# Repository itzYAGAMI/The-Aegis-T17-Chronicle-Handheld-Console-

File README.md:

# THE AEGIS-T17 CHRONICLE

*This is a pocket sized Steampunk inspired handheld gaming console featuring four games*

This is the repository for **The Aegis-T17 Chronicle**, a fully playable handheld console powered by the XIAO ESP32-C3 as the main brain. Housed in a 3D-printed steampunk casing with a voronoi design backplate, this device is a combination of steampunk aesthetics and embedded systems.

---

## The Games
The console features a main menu system that boots into four distinct games:

*   **Tamagotchi:** A pet simulator with stats like hunger, happiness and energy which decrease with time. Goal is to make the pet survive as long as possible.(Completed)
*   **Flappy Bird:** A copy of the famous Flappy Bird game. (Completed)
*   **Dino Run:** A copy of the classic infinite chrome dino run inifnite obstacles. (Completed)
*   **Platformer:** A platformer game with one level for now, will add more to it (Not completed)

---

## Hardware Specifications ("Steam Driven Electronics")
The Aegis-T17 was designed with a minimal footprint, utilizing the following hardware components:

*   MCU: XIAO ESP32-C3
*   Display: 0.96" SSD1306 OLED display (Resolution: 128x64)
*   Buttons: 3x Tactile Push Buttons
*   Sound: Passive Buzzer
*   Power Source: 3.7V 503040 LiPo Battery
*   Enclosure: 3D-printed Steampunk Casing having a snap fit battery compartment, voronoi patterned backplate, and a slot for a Button Compass for added steampunk vibe.
*   PCB: Custom designed PCB which houses all the parts on it and fits perfectly in the casing

### Prerequisites
*   Arduino IDE
*   Board Manager: esp32 by Espressif Systems (Select XIAO ESP32C3 at the top)
*   Library: Adafruit SSD1306 and Adafruit GFX Library

### Wiring Guide

*   **0.96" OLED Display:**Connect SDA to ESP32 Pin 5 | SCL to ESP32 Pin 6 | VCC to 3.3V | GND to GND
*   **Buttons (with INPUT_PULLUP):**
    *   Left Button to Pin 1
    *   Middle/Jump Button to Pin 2
    *   Right Button to Pin 3
*   **Piezo Buzzer:** Positive to Pin 10 | Ground to GND

### Installation
1. Clone or download this repository into your desired folder
2. Open the `main.ino` file in the Arduino IDE.
3. Make sure all `.cpp` and `.h` files are in the same folder.
4. Verify and Upload to the selected board.

---

## Credits
Designed by **SLIMER**.

*“Where steam-driven aesthetics meet modern electronics.”*
```eof

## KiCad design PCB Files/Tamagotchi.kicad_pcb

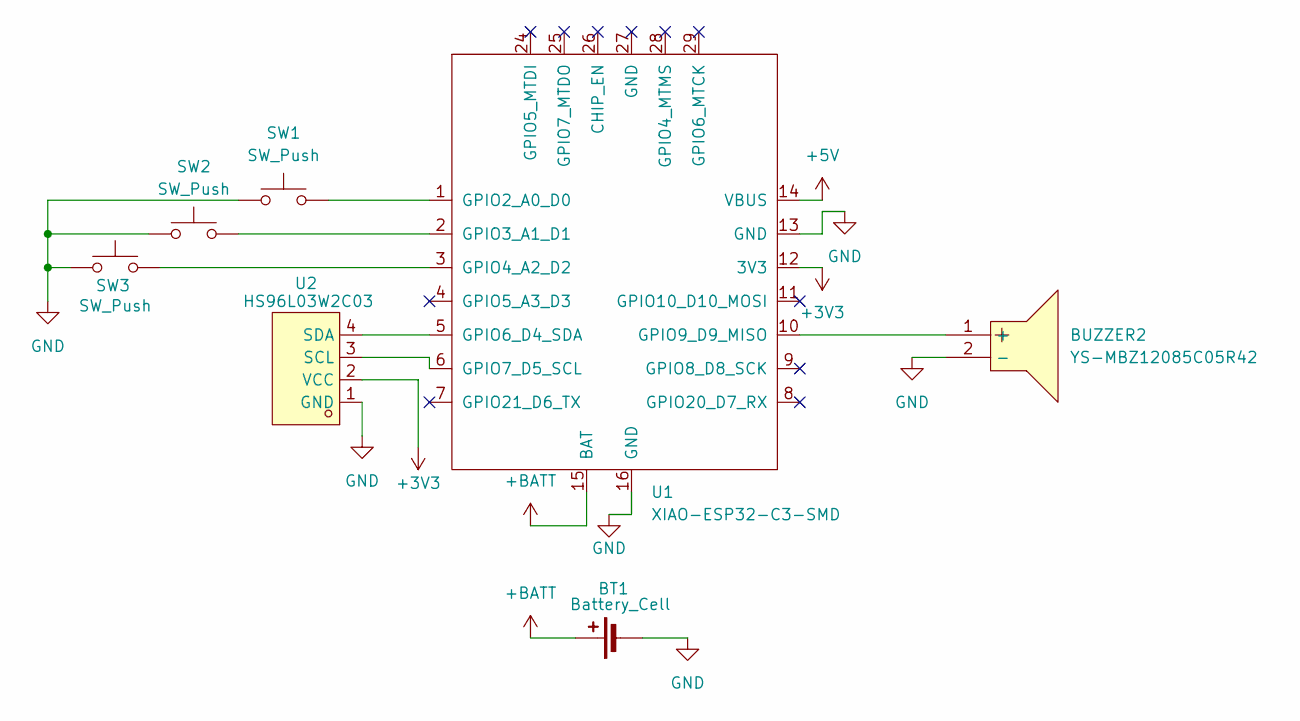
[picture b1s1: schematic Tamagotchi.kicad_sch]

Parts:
BT1: Battery_Cell; PinHeader_1x02_P2.54mm_Vertical
BUZZER2: YS-MBZ12085C05R42; BUZ-TH_BD12.0-P6.50-D0.6-FD; MPN YS-MBZ12085C05R42; LCSC Part C409842
SW1, SW2, SW3: SW_Push; SW_PUSH_6mm_H5mm
U1: XIAO-ESP32-C3-SMD; XIAO-ESP32-C3-DIP-SMD
U2: HS96L03W2C03; OLED-TH_L27.8-W27.2-P2.54_C9900033791; MPN HS96L03W2C03; LCSC Part C5248080

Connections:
+3V3: U1.12 (3V3), U2.2 (VCC)
+5V: U1.14 (VBUS)
+BATT: BT1.1 (+), U1.15 (BAT)
GND: BT1.2 (-), BUZZER2.2 (-), SW1.1, SW2.1, SW3.1, U1.13 (GND), U1.16 (GND), U2.1 (GND)
unnamed: BUZZER2.1 (+), U1.10 (GPIO9_D9_MISO)
unnamed: SW1.2, U1.1 (GPIO2_A0_D0)
unnamed: SW2.2, U1.2 (GPIO3_A1_D1)
unnamed: SW3.2, U1.3 (GPIO4_A2_D2)
unnamed: U1.5 (GPIO6_D4_SDA), U2.4 (SDA)
unnamed: U1.6 (GPIO7_D5_SCL), U2.3 (SCL)

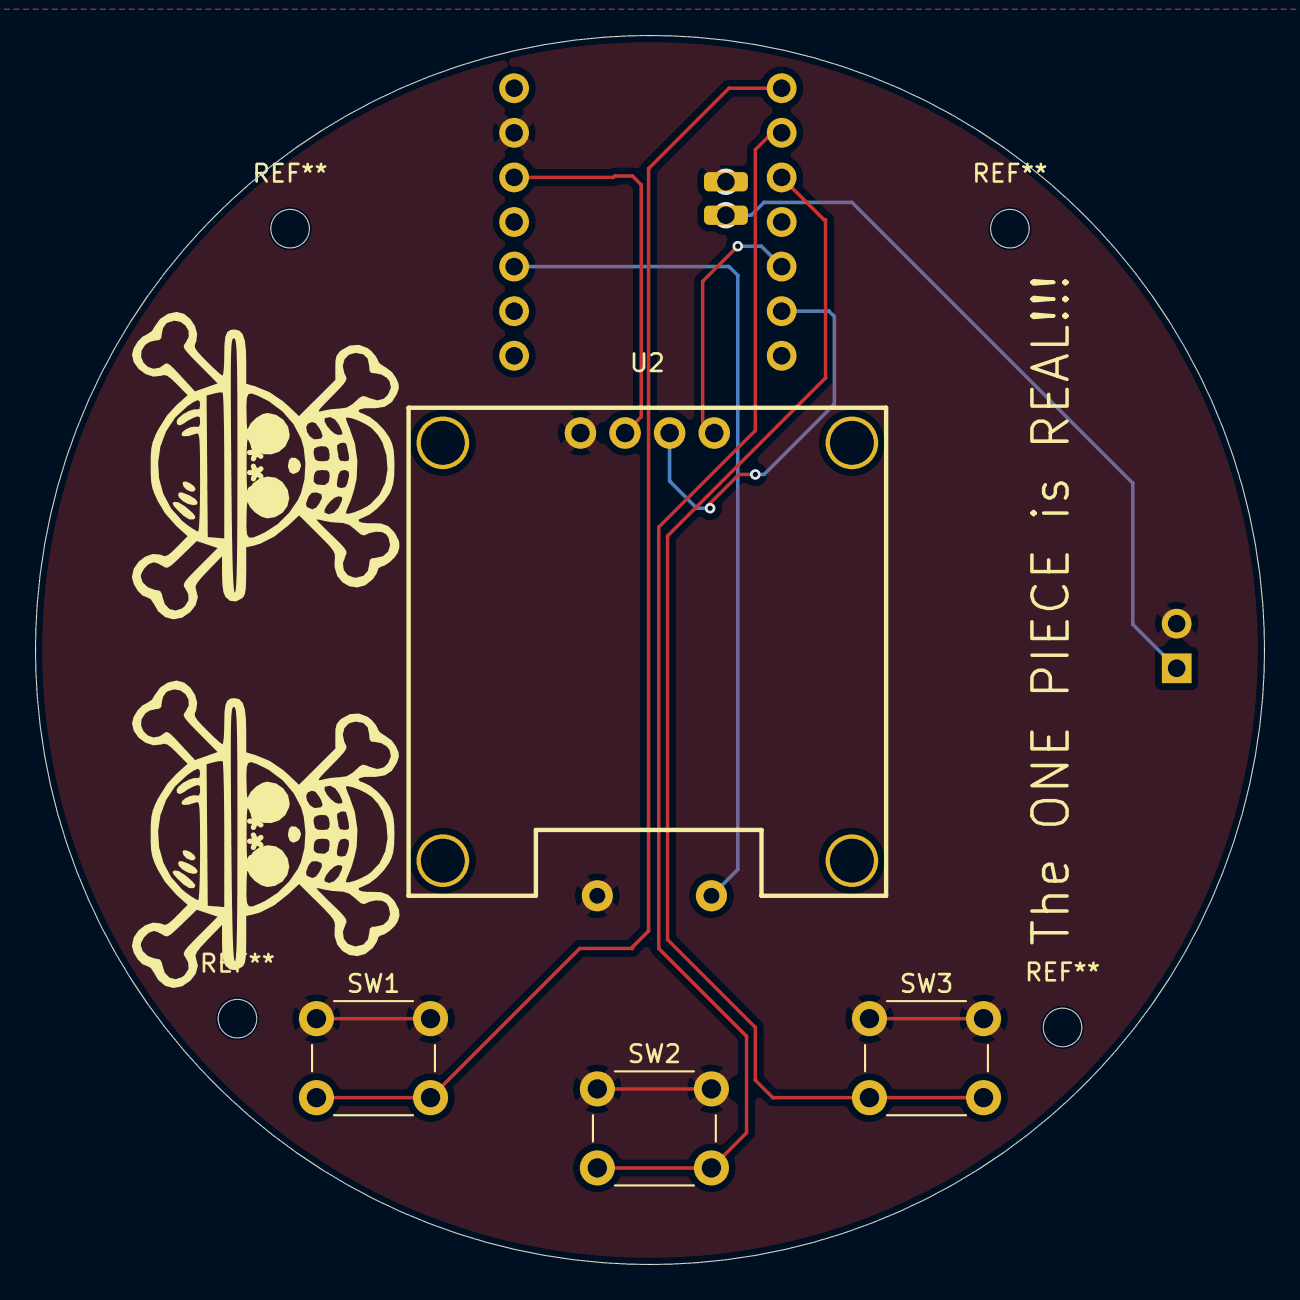
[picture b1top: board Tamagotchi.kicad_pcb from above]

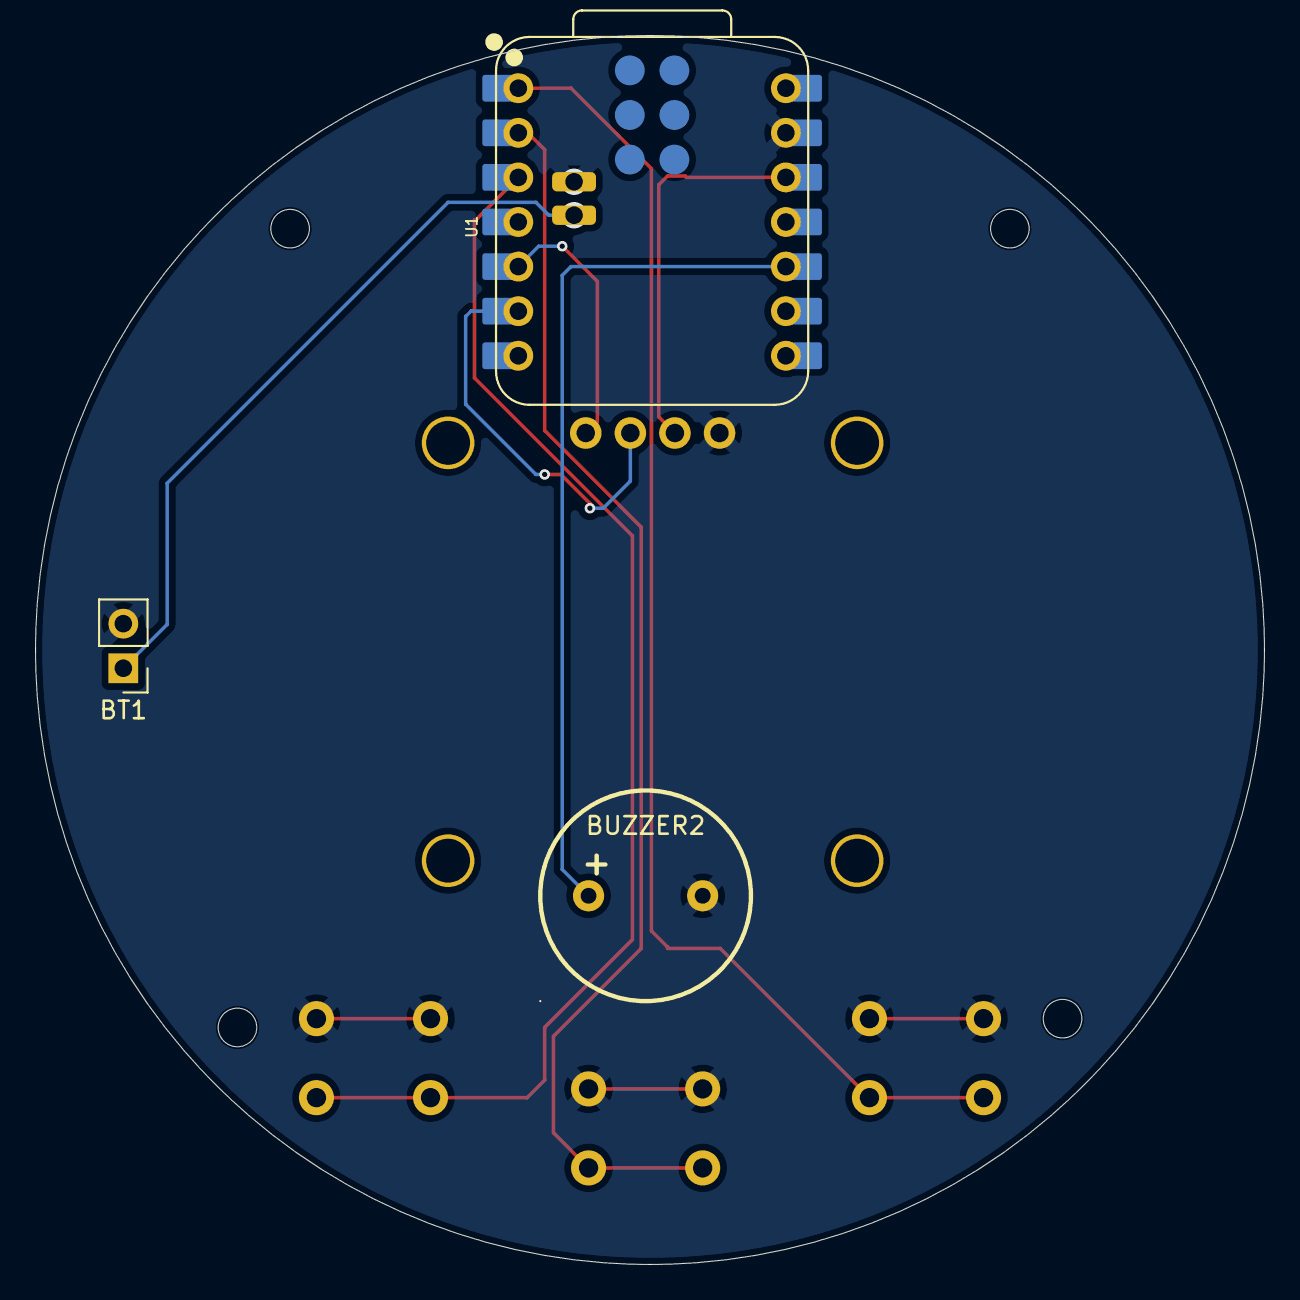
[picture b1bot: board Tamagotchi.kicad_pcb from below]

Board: 2 copper layers, 70.0 x 70.0 mm, 7 parts (3 on the bottom side), 9 nets.
